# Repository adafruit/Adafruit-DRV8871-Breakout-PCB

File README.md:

## Adafruit DRV8871 DC Motor Driver Breakout Board PCB
<a href="http://www.adafruit.com/products/3190"><br/>
Click here to purchase one from the Adafruit shop</a>

Crank up your robotics with powerful Adafruit DRV8871 motor driver breakout board. This motor driver has a lot of great specs that make it useful for a wide variety of mechatronics. In particular, the simple resistor-set current limiting and auto-magic PWM support make it super easy to use with just about any brushed DC motor.

PCB files for the Adafruit DRV8871 Breakout. The format is EagleCAD schematic and board layout
- https://www.adafruit.com/product/3190

### License

Adafruit invests time and resources providing this open source design, please support Adafruit and open-source hardware by purchasing products from [Adafruit](https://www.adafruit.com)!

All text above must be included in any redistribution

Designed by Limor Fried/Ladyada for Adafruit Industries.
Creative Commons Attribution/Share-Alike, all text above must be included in any redistribution. 
See license.txt for additional information.

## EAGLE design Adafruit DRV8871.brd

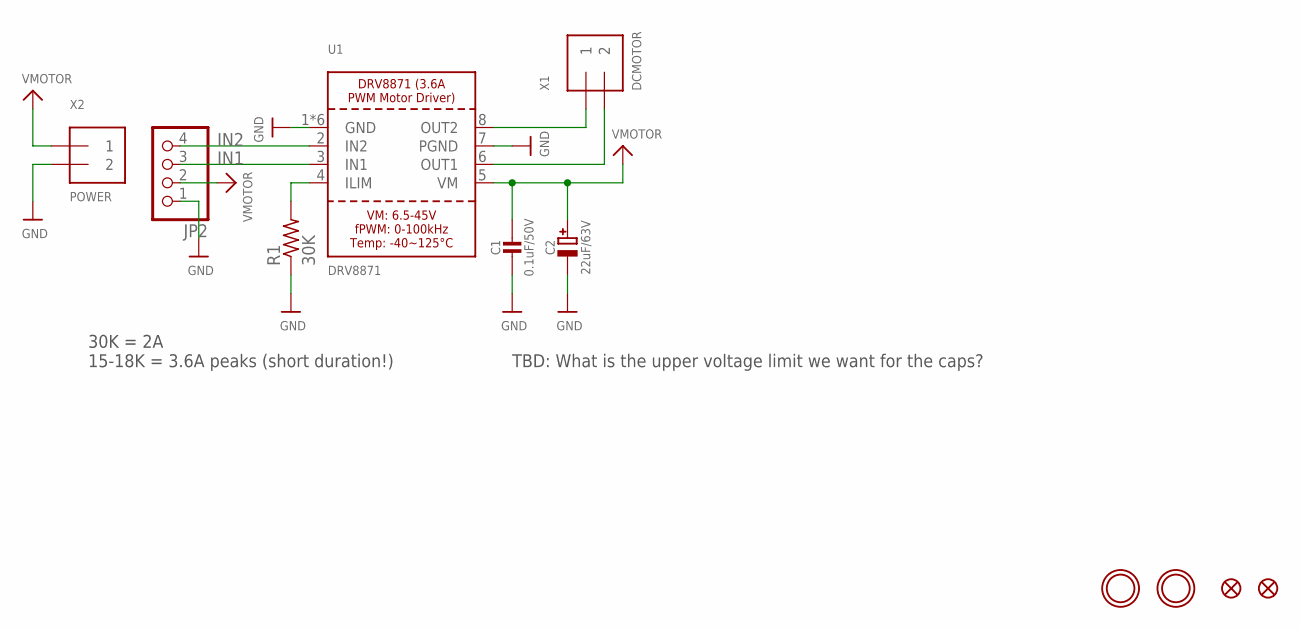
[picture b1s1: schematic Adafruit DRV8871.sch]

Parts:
C1: 0.1uF/50V; 0805-NO
C2: 22uF/63V; PANASONIC_D
FID1, FID2: FIDUCIAL""; FIDUCIAL_1MM
JP2: HEADER-1X476MIL; 1X04_ROUND_76
R1: 30K; 0805-THM
U1: DRV8871; HSOP8
U$9, U$10: MOUNTINGHOLE2.5; MOUNTINGHOLE_2.5_PLATED
X1: DCMOTOR; TERMBLOCK_1X2-3.5MM
X2: POWER; TERMBLOCK_1X2-3.5MM

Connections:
GND: C1.2, C2.-, JP2.1, R1.1, U1.1 (GND), U1.7 (PGND), U1.GND, U1.P$1 (GND), U1.P$2 (GND), U1.P$3 (GND), U1.P$4 (GND), X2.2
IN1: JP2.3, U1.3 (IN1)
IN2: JP2.4, U1.2 (IN2)
unnamed: R1.2, U1.4 (ILIM)
OUT1: U1.6 (OUT1), X1.2
OUT2: U1.8 (OUT2), X1.1
VMOTOR: C1.1, C2.+, JP2.2, U1.5 (VM), X2.1

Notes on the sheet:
TBD: What is the upper voltage limit we want for the caps?
30K = 2A 15-18K = 3.6A peaks (short duration!)

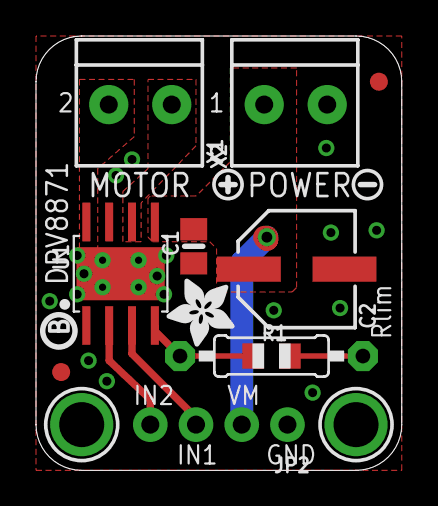
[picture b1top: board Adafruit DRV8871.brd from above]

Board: 2 copper layers, 20.3 x 24.1 mm, 15 parts (0 on the bottom side), 7 nets.

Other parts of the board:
U$11: SYMBOL_PLUS
U$12: SYMBOL_MINUS
U$14: ADAFRUIT_3.5MM
U$15: PCBFEAT-REV-040

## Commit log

2016-07-06 initdrv

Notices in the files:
parts and their libraries:
microbuilder: This work is placed in the public domain, and may be freely used for commercial and non-commercial work with the following conditions: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
